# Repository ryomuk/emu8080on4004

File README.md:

# emu8080on4004
Intel 8080 Emulator on 4004 Evaluation Board

This document is written mostly in Japanese.
If necessary, please use a translation service such as DeepL (I recommend this) or Google.

## 概要
自作の4004実験用ボードと，その上で動作する8080エミュレータです．Palo Alot Tiny BASIC(4K整数型BASIC)や，Grant Searle's BASIC(8K浮動小数点BASIC)の8080移植版がほぼそのまま動くレベルの機能が実現できています．動作速度は8080実機の1/700程度です．

## 制限事項等
- P(パリティ)フラグの実装は正確ではありません．{J,C,R}{PO,PE}実行時にAレジスタの値から計算されます．
- DAA命令の実装は正確ではありません．
- IN命令(コントロールレジスタ)はACC=0xFF(データあり)を返します．
- IN命令(データレジスタ)は4004ボードのソフトウェアで実装されたUARTのGETCHARを呼ぶので，入力されるまで止まります．
- OUT命令はAレジスタを4004ボードのシリアルポートに出力します．
- 割り込み関連命令(DI, EI)は未実装です．

## 実験ボードの仕様
### ブレッドボード版プロトタイプの仕様
- CPU: Intel 4004
- Clock: 740kHz
- DATA RAM: 4002-1 x 2 + 4002-2 x 2 (計320bit x 4)
- Program Memory
  - ROM: AT28C64B (8k x 8bit EEPROM)
    - 000H〜EFFHの3.75KB利用可能
  - RAM: HM6268(4k x 4bit SRAM)x 2個
    - 物理メモリ F00H〜FFDHの254byte x 16バンク
      (上記を論理メモリ 000H〜FDFHにマッピングしてアクセス)
- 通信ポート: 9600bps Software Serial UART (TTL level)

### Rev.2.1版の仕様(ブレッドボード版との差分)
- Program Memory
  - DATA RAM: ピンヘッダの設定により4002-1 x 4の構成も可能ですが，その場合はソフトウェアでRAM2, RAM3をアクセスしている部分を修正する必要があります．
  - ROM: AT28C64B, AT28C256, 2764, 27256をDIPスイッチで選択可能なように設計しましたが，動作確認はAT28C64Bで実施．それ以外は未確認です．
  - RAM: HM624256(1Mbit(256k x 4bit) SRAM)x 2個
    - 物理メモリ F00H〜FFDHの254byte x 256バンク
      (上記を論理メモリ 0000H〜FDFFHにマッピングしてアクセス)

## ToDO
- メモリ64KBに拡張 → Rev.2.1で実現(2023/4/12)
- プリント基板作成 → Rev.2.1で実現(2023/4/12)
- IN命令時にTESTキーを使ったSTOPボタン相当の機能の実装

## 動画
Youtubeで関連動画を公開しています．
- https://www.youtube.com/@ryomukai/videos

## ブログ
関連する情報が書いてあるかも．
- [Intel 4004関連記事のまとめ](https://note.com/ryomuk/m/m2f55e2a1f586)

## 4004関連開発事例
- [Intel 4004  50th Anniversary Project](https://www.4004.com/)
  - https://www.4004.com/busicom-replica.html
  - http://www.4004.com/2009/Busicom-141PF-Calculator_asm_rel-1-0-1.txt
- https://github.com/jim11662418/4004-SBC
- https://www.cpushack.com/mcs-4-test-boards-for-sale
- https://github.com/novi/4004MainBoard

## データシート
- http://www.bitsavers.org/components/intel/
- https://www.intel-vintage.info/intelmcs.htm

## 開発環境
- [The Macroassembler AS](http://john.ccac.rwth-aachen.de:8000/as/)

## 画像集
- ブレッドボード版のプロトタイプ

- プロトタイプでPalo Alto BASIC実行

- Rev.2.1基板

- ブレッドボード版とRev.2.1基板

- 8K BASIC 起動画面

## 更新履歴
- 2023/3/21: 初版公開
- 2023/4/3: SUBフラグ(NEC uPD8080A, uCOM-80用)に関するコードを削除
- 2023/4/12: 基板(Rev.2.1)に合わせていろいろ更新．ブレッドボード版はprototypeフォルダに移動
- 2023/4/15: emu.asmにレジスタ表示しながらの連続実行とTESTボタンでの停止機能を追加
- 2023/4/16: ADC, ACIにバグ(0+FFH+Carrry(1)でCarryが立たない)があったので修正．

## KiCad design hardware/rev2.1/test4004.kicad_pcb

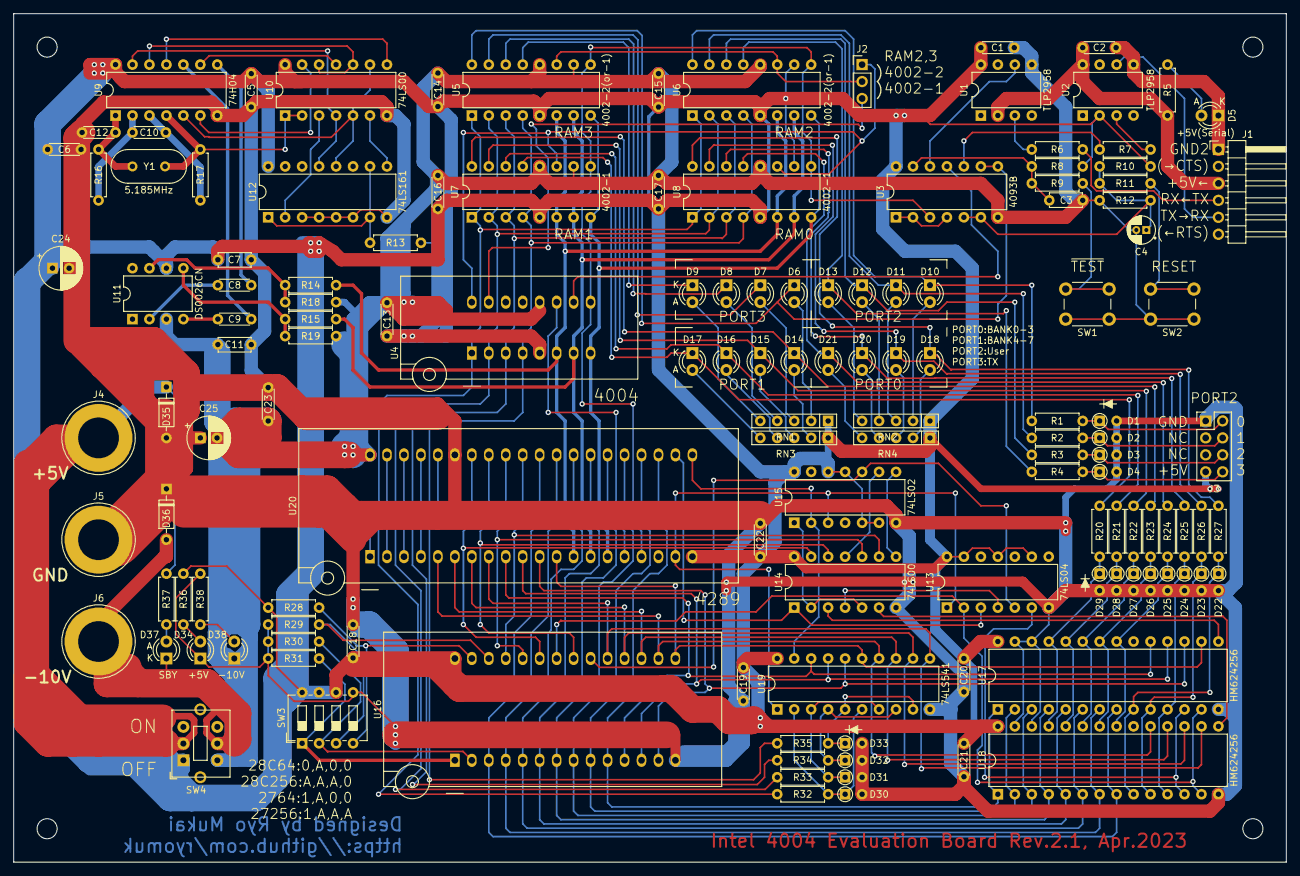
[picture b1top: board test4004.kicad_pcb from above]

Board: 2 copper layers, 190.5 x 127.0 mm, 140 parts (0 on the bottom side), 142 nets.

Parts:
C1, C2, C5, C6, C13, C14, C15, C16, C17, C18, C19, C20, C21, C22, C23: 0.1uF; C_Disc_D4.3mm_W1.9mm_P5.00mm
C3, C7, C11: 1uF; C_Disc_D4.7mm_W2.5mm_P5.00mm
C4: 10uF; CP_Radial_D4.0mm_P1.50mm
C8, C9, C10: 0.01uF; C_Disc_D4.3mm_W1.9mm_P5.00mm
C12: 50pF; C_Disc_D4.3mm_W1.9mm_P5.00mm
C24, C25: 47uF; CP_Radial_D6.3mm_P2.50mm
D1, D2, D3, D4, D22, D23, D24, D25, D26, D27, D28, D29, D30, D31, D32, D33: 1N4148; D_DO-35_SOD27_P2.54mm_Vertical_AnodeUp
D5: YELLOW; LED_D3.0mm
D6, D7, D8, D9, D10, D11, D12, D13, D14, D15, D16, D17, D18, D19, D20, D21: LED; LED_D3.0mm
D34: TLR101; LED_D3.0mm
D35: Zener6.2V; D_DO-35_SOD27_P7.62mm_Horizontal
D36: Zener12V; D_DO-35_SOD27_P7.62mm_Horizontal
D37: RED; LED_D3.0mm
D38: TLG101; LED_D3.0mm
H1, H2, H3, H4: MountingHole; MountingHole_3mm
J1: UART(TTL); PinHeader_1x06_P2.54mm_Horizontal
J2: Pin Header 3P; PinHeader_1x03_P2.54mm_Vertical
J3: PORT2; PinHeader_2x04_P2.54mm_Vertical
J4: +5V; Banana_Jack_1Pin
J5: GND; Banana_Jack_1Pin
J6: -10V; Banana_Jack_1Pin
R1, R2, R3, R4, R7, R32, R33, R34, R35: 4.7k; R_Axial_DIN0207_L6.3mm_D2.5mm_P7.62mm_Horizontal
R5: 47k; R_Axial_DIN0207_L6.3mm_D2.5mm_P7.62mm_Horizontal
R6, R9, R11, R13: 1k; R_Axial_DIN0207_L6.3mm_D2.5mm_P7.62mm_Horizontal
R8, R10, R20, R21, R22, R23, R24, R25, R26, R27: 10k; R_Axial_DIN0207_L6.3mm_D2.5mm_P7.62mm_Horizontal
R12, R28, R29, R30, R31, R37: 100k; R_Axial_DIN0207_L6.3mm_D2.5mm_P7.62mm_Horizontal
R14, R15: 110; R_Axial_DIN0207_L6.3mm_D2.5mm_P7.62mm_Horizontal
R16, R17: 820; R_Axial_DIN0207_L6.3mm_D2.5mm_P7.62mm_Horizontal
R18, R19: 5.6k; R_Axial_DIN0207_L6.3mm_D2.5mm_P7.62mm_Horizontal
R36, R38: 470; R_Axial_DIN0207_L6.3mm_D2.5mm_P7.62mm_Horizontal
RN1, RN2, RN3, RN4: 100k; R_Array_SIP5
SW1: ~{TEST}; SW_PUSH_6mm_H4.3mm
SW2: RESET; SW_PUSH_6mm_H4.3mm
SW3: SW_DIP_x04; SW_DIP_SPSTx04_Slide_6.7x11.72mm_W7.62mm_P2.54mm_LowProfile
SW4: SW_DPDT; SW_DPDT_Toggle_with_mount
U1, U2: TLP2958; DIP-8_W7.62mm
U3: 4093B; DIP-14_W7.62mm
U4: 4004_CPU; DIP_Socket-16_W4.3_W5.08_W7.62_W10.16_W10.9_3M_216-3340-00-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
U5, U6: 4002-2(or-1); DIP-16_W7.62mm
U7, U8: 4002-1; DIP-16_W7.62mm
U9: 74H04; DIP-14_W7.62mm
U10, U14: 74LS00; DIP-14_W7.62mm
U11: DS0026CN; DIP-8_W7.62mm
U12: 74LS161; DIP-16_W7.62mm
U13: 74LS04; DIP-14_W7.62mm
U15: 74LS02; DIP-14_W7.62mm
U16: 28C64B; DIP_Socket-28_W11.9_W12.7_W15.24_W17.78_W18.5_3M_228-1277-0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
U17, U18: HM624256; DIP-28_W10.16mm
U19: 74LS541; DIP-20_W7.62mm
U20: 4289_MEMORY_IF; DIP_Socket-40_W11.9_W12.7_W15.24_W17.78_W18.5_3M_240-1280-0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
Y1: 5.185MHz; Crystal_HC49-U_Vertical

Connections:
+5V: C1.2, C5.1, C6.1, C7.2, C13.1, C14.1, C15.1, C16.1, C17.1, C18.1, C19.1, C20.1, C21.1, C22.1, C24.1, J3.7, R8.1, R10.1, R13.2, R28.2, R36.1, RN1.1 (common), RN2.1 (common), RN3.1 (common), RN4.1 (common), SW3.6, SW3.7, SW3.8, SW4.1 (A), U1.8 (VDD), U2.2 (A), U3.14 (Vdd), U4.5 (Vss), U5.5 (Vss), U6.5 (Vss), U6.10 (P0), U7.5 (Vss), U8.5 (Vss), U8.10 (P0), U9.14 (VCC), U10.14 (VCC), U11.6 (V+), U12.16 (VCC), U13.9, U13.11, U13.13, U13.14 (VCC), U14.14 (VCC), U15.5, U15.6, U15.11, U15.12, U15.14 (VCC), U16.28 (Vdd), U17.28 (Vcc), U18.28 (Vcc), U19.20 (VCC), U20.20 (Vss)
-10V: C1.1, C3.2, C4.2, C11.2, C13.2, C14.2, C15.2, C16.2, C17.2, C23.2, C25.2, D38.1 (K), R12.2, R18.1, R19.1, SW1.1, SW2.1, SW4.4 (A), U1.5 (GND), U3.7 (Vss), U4.12 (Vdd), U5.10 (P0), U5.12 (Vdd), U6.12 (Vdd), U7.10 (P0), U7.12 (Vdd), U8.12 (Vdd), U11.3 (V-), U20.40 (Vdd)
/ClockGen/CLK1: R14.2, U4.6 (CLK1), U5.6 (CLK1), U6.6 (CLK1), U7.6 (CLK1), U8.6 (CLK1), U20.13 (CLK1)
/ClockGen/CLK2: R15.2, U4.7 (CLK2), U5.7 (CLK2), U6.7 (CLK2), U7.7 (CLK2), U8.7 (CLK2), U20.14 (CLK2)
/ProgramMemory/CM: U4.11 (CMROM), U20.16 (CM)
/ProgramMemory/D0: U4.1 (D0), U5.1 (D0), U6.1 (D0), U7.1 (D0), U8.1 (D0), U20.1 (D0)
/ProgramMemory/D1: U4.2 (D1), U5.2 (D1), U6.2 (D1), U7.2 (D1), U8.2 (D1), U20.2 (D1)
/ProgramMemory/D2: U4.3 (D2), U5.3 (D2), U6.3 (D2), U7.3 (D2), U8.3 (D2), U20.3 (D2)
/ProgramMemory/D3: U4.4 (D3), U5.4 (D3), U6.4 (D3), U7.4 (D3), U8.4 (D3), U20.4 (D3)
/ProgramMemory/RESET: U3.3, U4.9 (RESET), U5.9 (RESET), U6.9 (RESET), U7.9 (RESET), U8.9 (RESET), U20.17 (RESET)
/ProgramMemory/SYNC: U4.8 (SYNC), U5.8 (SYNC), U6.8 (SYNC), U7.8 (SYNC), U8.8 (SYNC), U20.15 (SYNC)
BANK0: D18.1 (K), R27.1, U8.16 (O0)
BANK1: D19.1 (K), R26.1, U8.15 (O1)
BANK2: D20.1 (K), R25.1, U8.14 (O2)
BANK3: D21.1 (K), R24.1, U8.13 (O3)
BANK4: D14.1 (K), R23.1, U7.16 (O0)
BANK5: D15.1 (K), R22.1, U7.15 (O1)
BANK6: D16.1 (K), R21.1, U7.14 (O2)
BANK7: D17.1 (K), R20.1, U7.13 (O3)
C0: U14.9, U16.25 (A8), U20.31 (C0)
C1: U14.10, U16.24 (A9), U20.32 (C1)
C2: U14.12, U16.21 (A10), U20.33 (C2)
C3: U14.13, U16.23 (A11), U20.34 (C3)
CMRAM0: J2.1, U4.16 (CMRAM0), U7.11 (CM), U8.11 (CM)
CMRAM1: J2.3, U4.15 (CMRAM1)
CM_RAM23: J2.2, U5.11 (CM), U6.11 (CM)
GND: C5.2, C6.2, C7.1, C11.1, C12.2, C18.2, C19.2, C20.2, C21.2, C22.2, C23.1, C24.2, C25.1, D1.2 (A), D2.2 (A), D3.2 (A), D4.2 (A), D22.2 (A), D23.2 (A), D24.2 (A), D25.2 (A), D26.2 (A), D27.2 (A), D28.2 (A), D29.2 (A), D30.2 (A), D31.2 (A), D32.2 (A), D33.2 (A), D34.1 (K), D35.2 (A), D36.1 (K), J3.1, J5.1, R29.1, R30.1, R31.1, R38.1, SW3.5, U9.7 (GND), U10.7 (GND), U12.3 (A), U12.4 (B), U12.5 (C), U12.6 (D), U12.8 (GND), U13.7 (GND), U14.7 (GND), U15.7 (GND), U16.14 (Vss(GND)), U17.14 (Vss(GND)), U17.26 (A16), U17.27 (A17), U18.14 (Vss(GND)), U18.26 (A16), U18.27 (A17), U19.10 (GND), U20.35 (Vdd1)
GND2: C2.1, D5.1 (K), J1.1, U2.5 (GND)
unnamed: C3.1, R8.2, R9.2, U3.13
unnamed: C4.1, R10.2, R11.2, R12.1, U3.5, U3.6
unnamed: C8.1, U9.8
unnamed: C9.1, U9.10
unnamed: C10.1, R16.2, U9.2
unnamed: C10.2, R17.1, U9.3
unnamed: C12.1, R16.1, U9.1, Y1.1
unnamed: D1.1 (K), J3.2, R1.2
unnamed: D2.1 (K), J3.4, R2.2
unnamed: D3.1 (K), J3.6, R3.2
unnamed: D4.1 (K), J3.8, R4.2
unnamed: D5.2 (A), R5.1
unnamed: D6.2 (A), RN1.2 (R1)
unnamed: D6.1 (K), U3.8, U3.9, U5.16 (O0)
unnamed: D7.2 (A), RN1.3 (R2)
unnamed: D7.1 (K), U5.15 (O1)
unnamed: D8.2 (A), RN1.4 (R3)
unnamed: D8.1 (K), U5.14 (O2)
unnamed: D9.2 (A), RN1.5 (R4)
unnamed: D9.1 (K), U5.13 (O3)
unnamed: D10.2 (A), RN2.2 (R1)
unnamed: D11.2 (A), RN2.3 (R2)
unnamed: D12.2 (A), RN2.4 (R3)
unnamed: D13.2 (A), RN2.5 (R4)
unnamed: D14.2 (A), RN3.2 (R1)
unnamed: D15.2 (A), RN3.3 (R2)
unnamed: D16.2 (A), RN3.4 (R3)
unnamed: D17.2 (A), RN3.5 (R4)
unnamed: D18.2 (A), RN4.2 (R1)
unnamed: D19.2 (A), RN4.3 (R2)
unnamed: D20.2 (A), RN4.4 (R3)
unnamed: D21.2 (A), RN4.5 (R4)
unnamed: D22.1 (K), R27.2, U17.9 (A8), U18.9 (A8)
unnamed: D23.1 (K), R26.2, U17.10 (A9), U18.10 (A9)
unnamed: D24.1 (K), R25.2, U17.11 (A10), U18.11 (A10)
unnamed: D25.1 (K), R24.2, U17.21 (A11), U18.21 (A11)
unnamed: D26.1 (K), R23.2, U17.22 (A12), U18.22 (A12)
unnamed: D27.1 (K), R22.2, U17.23 (A13), U18.23 (A13)
unnamed: D28.1 (K), R21.2, U17.24 (A14), U18.24 (A14)
unnamed: D29.1 (K), R20.2, U17.25 (A15), U18.25 (A15)
unnamed: D30.1 (K), R32.2, U19.2 (A0), U19.6 (A4)
unnamed: D31.1 (K), R33.2, U19.3 (A1), U19.7 (A5)
unnamed: D32.1 (K), R34.2, U19.4 (A2), U19.8 (A6)
unnamed: D33.1 (K), R35.2, U19.5 (A3), U19.9 (A7)
unnamed: D34.2 (A), R36.2
unnamed: D35.1 (K), J4.1, R37.1, SW4.2 (B)
unnamed: D36.2 (A), D37.1 (K), J6.1, SW4.5 (B)
unnamed: D37.2 (A), R37.2
unnamed: D38.2 (A), R38.2
unnamed: J1.4, R6.1
unnamed: J1.5, U2.6 (Vo)
unnamed: R7.1, U3.10
unnamed: R9.1, SW1.2
unnamed: R11.1, SW2.2
unnamed: R17.2, U9.4, U10.1, U10.2, Y1.2
unnamed: R6.2, U1.3 (K)
unnamed: U1.6 (Vo), U3.12
unnamed: R7.2, U2.3 (K)
unnamed: U3.1, U3.2, U3.4
unnamed: U3.11, U4.10 (TEST)
unnamed: U9.11, U10.8
unnamed: U9.12, U10.10, U10.12
unnamed: U9.9, U10.11
unnamed: U9.6, U10.13
unnamed: C8.2, U11.2 (IN_A)
unnamed: C9.2, U11.4 (IN_B)
unnamed: R14.1, R18.2, U11.7 (OUT_A)
unnamed: R15.1, R19.2, U11.5 (OUT_B)
unnamed: U10.3, U12.2 (CLOCK)
unnamed: R13.1, U12.1 (~CLEAR), U12.7 (EP), U12.10 (ET)
unnamed: U10.6, U12.9 (LOAD)
unnamed: U9.13, U10.4, U12.13 (QB)
unnamed: U9.5, U10.5, U10.9, U12.12 (QC)
unnamed: U13.4, U14.4
unnamed: U14.2, U14.5, U15.1
unnamed: U14.8, U15.8
unnamed: U14.11, U15.9
unnamed: U16.10 (A0), U17.1 (A0), U18.1 (A0), U20.23 (A0)
unnamed: U16.9 (A1), U17.2 (A1), U18.2 (A1), U20.24 (A1)
unnamed: U16.8 (A2), U17.3 (A2), U18.3 (A2), U20.25 (A2)
unnamed: U16.7 (A3), U17.4 (A3), U18.4 (A3), U20.26 (A3)
unnamed: U16.6 (A4), U17.5 (A4), U18.5 (A4), U20.27 (A4)
unnamed: U16.5 (A5), U17.6 (A5), U18.6 (A5), U20.28 (A5)
unnamed: U16.4 (A6), U17.7 (A6), U18.7 (A6), U20.29 (A6)
unnamed: U16.3 (A7), U17.8 (A7), U18.8 (A7), U20.30 (A7)
unnamed: U16.11 (D0), U17.19 (I/O1), U19.18 (Y0), U20.9 (OPA0)
unnamed: U16.12 (D1), U17.18 (I/O2), U19.17 (Y1), U20.10 (OPA1)
unnamed: U16.13 (D2), U17.17 (I/O3), U19.16 (Y2), U20.11 (OPA2)
unnamed: U16.15 (D3), U17.16 (I/O4), U19.15 (Y3), U20.12 (OPA3)
unnamed: U16.16 (D4), U18.19 (I/O1), U19.14 (Y4), U20.5 (OPR0)
unnamed: U16.17 (D5), U18.18 (I/O2), U19.13 (Y5), U20.6 (OPR1)
unnamed: U16.18 (D6), U18.17 (I/O3), U19.12 (Y6), U20.7 (OPR2)
unnamed: U16.19 (D7), U18.16 (I/O4), U19.11 (Y7), U20.8 (OPR3)
unnamed: U13.1, U15.3, U19.1 (G1), U20.19 (OUT)
unnamed: U15.2, U19.19 (G2), U20.21 (PM)
unnamed: U13.3, U14.1, U20.22 (FL)
unnamed: R32.1, U20.39 (I/O1)
unnamed: R33.1, U20.38 (I/O2)
unnamed: R34.1, U20.37 (I/O3)
unnamed: R35.1, U20.36 (I/O4)
RAM2-0: D10.1 (K), R1.1, U6.16 (O0)
RAM2-1: D11.1 (K), R2.1, U6.15 (O1)
RAM2-2: D12.1 (K), R3.1, U6.14 (O2)
RAM2-3: D13.1 (K), R4.1, U6.13 (O3)
ROM_P1: R31.2, SW3.1, U16.1 (NC)
ROM_P2: R30.2, SW3.2, U16.2 (A12)
ROM_P26: R29.2, SW3.3, U16.26 (NC)
ROM_P27: R28.1, SW3.4, U16.27 (~WE)
VBUS: C2.2, J1.3, R5.2, U1.2 (A), U2.8 (VDD)
~CS_RAM: U13.6, U17.12 (~CS), U18.12 (~CS)
~CS_ROM: U13.5, U15.10, U16.20 (~CS)
~OE: U13.2, U16.22 (~OE), U17.13 (~OE), U18.13 (~OE)
~WE_OPA: U14.3, U17.15 (~WE)
~WE_OPR: U14.6, U18.15 (~WE)

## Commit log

2023-03-21 reduced image size
2023-03-22 small fix
2023-04-03 minor modification
2023-04-03 add errorcheck in getline
2023-04-08 README.md updated
2023-04-15 emu.asm updated
2023-04-16 bug fixed
2023-04-17 README updated
